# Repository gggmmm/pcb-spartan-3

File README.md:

# pcb-spartan-3

First attempt at PCB design using KiCad 5.1. This design contains Xilinx Spartan-3 programmable either through JTAG or Atmega328p.

Eeschema produces some warnings, due to the fact I have used different grids, which I learned later to be discouraged.

In the library, there are more footprints/models than actually used. I did not remove the unused ones.

Tested only on Windows 10.

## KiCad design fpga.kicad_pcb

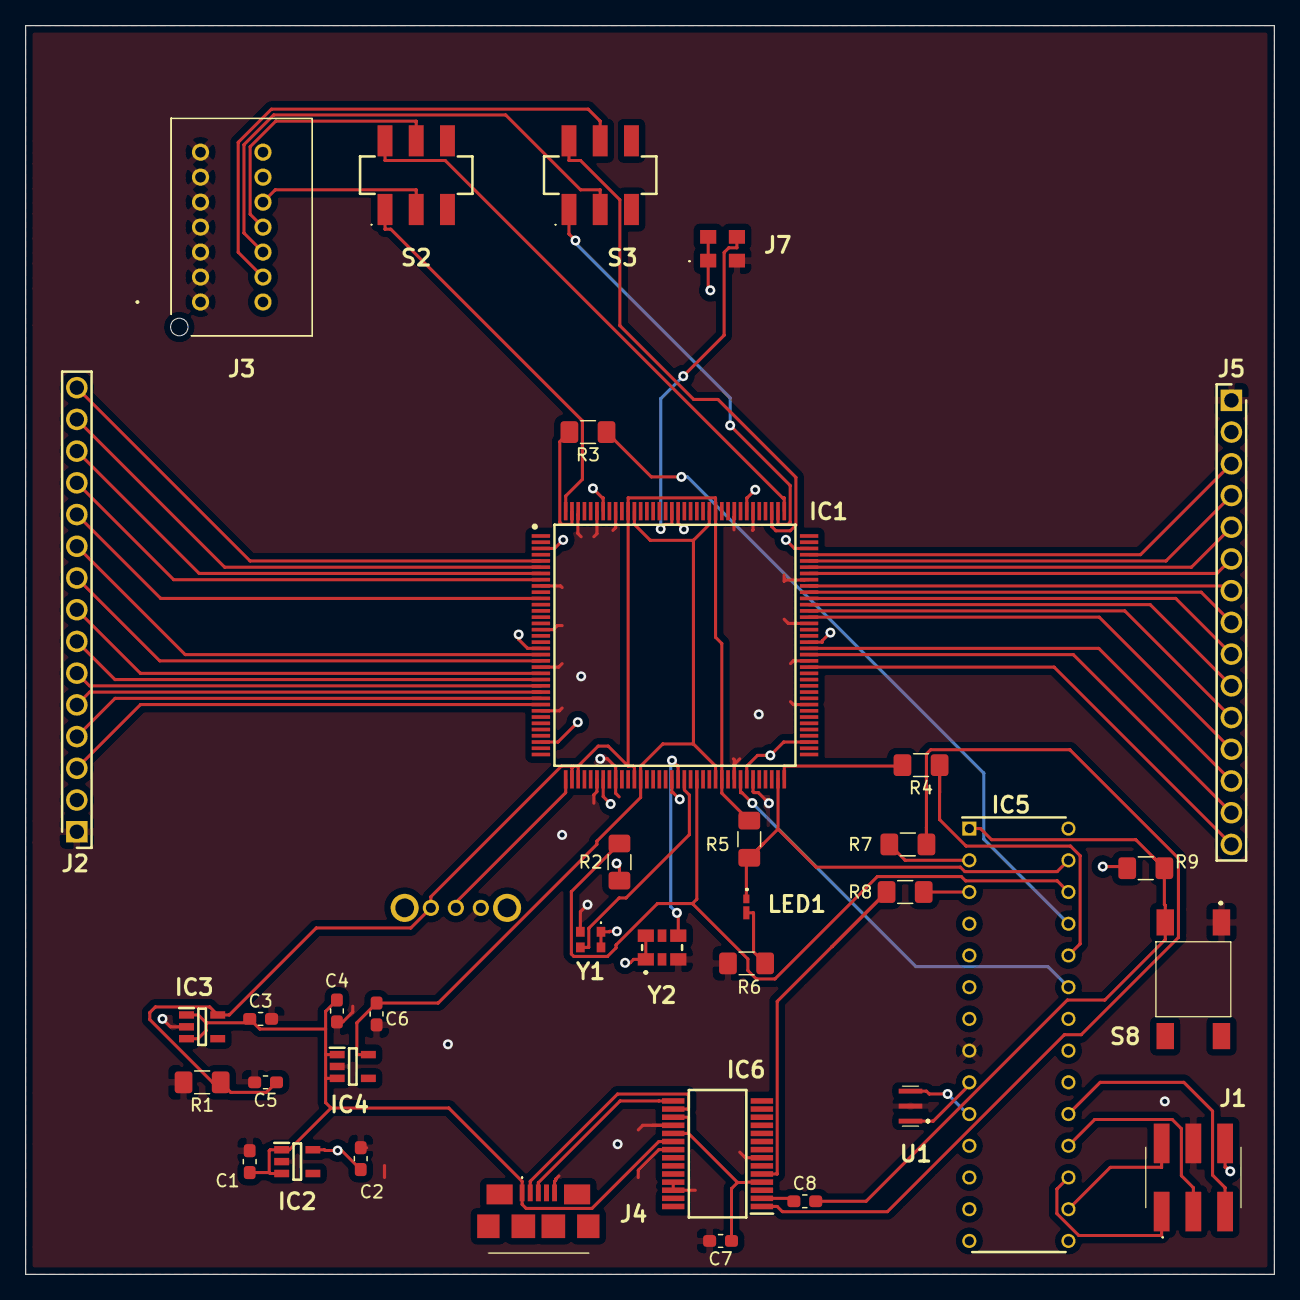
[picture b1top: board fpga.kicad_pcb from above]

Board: 4 copper layers, 100.0 x 100.0 mm, 37 parts (1 on the bottom side), 66 nets.

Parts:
C1, C2, C3, C4, C5, C6: 1uF; C_0603_1608Metric_Pad1.05x0.95mm_HandSolder
C7, C8: 100nF; C_0603_1608Metric_Pad1.05x0.95mm_HandSolder
IC1: XC3S200-4TQG144C; QFP50P2200X2200X160-144N
IC2: MIC5504-3.3YM5-TR; SOT95P280X145-5N
IC3: MIC5504-2.5YM5-T5; SOT95P280X145-5N
IC4: MIC5504-1.2YM5-TR; SOT95P280X130-5N
IC5: ATMEGA328P-PU; DIP794W53P254L3467H457Q28N
IC6: FT232RL-TUBE; SOP65P780X200-28N
J1: ICSP; 10129383906002ALF
J2: BANK 6/7; HDRV15W67P0X254_1X15_3785X236X1117P
J3: 55917-1410; 559171410
J4: ZX62-B-5PA_33_; ZX62B5PA33
J5: BANK 2/3; HDRV15W67P0X254_1X15_3785X236X1117P
J7: OSC 32.768 kHz; ECS327MVATX3CNTR
LED1: KG_DELLS1.22-JGKH-24; KGDELLS122JGKH24
R1, R3, R4: 68; R_1206_3216Metric_Pad1.42x1.75mm_HandSolder
R2: 4.7K; R_1206_3216Metric_Pad1.42x1.75mm_HandSolder
R5, R6: 330; R_1206_3216Metric_Pad1.42x1.75mm_HandSolder
R7, R8: 1K; R_1206_3216Metric_Pad1.42x1.75mm_HandSolder
R9: 10K; R_1206_3216Metric_Pad1.42x1.75mm_HandSolder
S1: M1_SW; OS102011MA1QN1
S2: SW_TDI_TDO; JS202011SCQN
S3: SW_TCK_TMS; JS202011SCQN
S8: LL3301NF065QG
U1: RESON_8M; CSTNE16M0V530000R0
Y1: OSC 50 MHz; DSC6101JL3B0500000
Y2: OSC 200 MHz; XLH335200000000X

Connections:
+1V2: C6.1, IC1.49, IC1.61, IC1.121, IC1.133, IC4.5
+2V5: C5.1, IC1.38, IC1.39, IC1.48, IC1.62, IC1.120, IC1.134, IC3.5, R1.1, R5.2, S1.1
+3V3: C2.1, IC1.3, IC1.19, IC1.34, IC1.43, IC1.54, IC1.66, IC1.75, IC1.91, IC1.106, IC1.115, IC1.126, IC1.138, IC2.5, IC5.7, IC5.20, J1.B3, J2.2, J3.2, J5.2, J7.1, J7.4, R2.1, R9.2, Y1.1, Y1.4, Y2.1, Y2.6
CCLK: IC5.24, R4.1
D+: IC6.15, J4.3
D-: IC6.16, J4.2
DIN_DO: IC1.65, IC5.23
DONE: IC1.71, IC5.27, LED1.1, R5.1
DTR: C8.1, IC6.2
GND: C1.2, C2.2, C3.2, C4.2, C5.2, C6.2, C7.2, IC1.9, IC1.16, IC1.22, IC1.29, IC1.42, IC1.45, IC1.64, IC1.67, IC1.81, IC1.88, IC1.94, IC1.101, IC1.114, IC1.117, IC1.136, IC1.139, IC1.142, IC2.2, IC3.2, IC4.2, IC5.8, IC5.22, IC6.7, IC6.18, IC6.21, IC6.25, IC6.26, J1.B2, J2.1, J3.1, J3.3, J3.5, J3.7, J3.9, J3.11, J3.13, J4.5, J5.1, J7.2, R1.2, R6.1, S1.3, S8.1, U1.2, Y1.2, Y2.3
INIT_B: IC1.58, IC5.26, R2.2
IO_L20N_2: IC1.105, J5.3
IO_L20N_7: IC1.6, J2.14
IO_L20P_2: IC1.104, J5.4
IO_L20P_7: IC1.5, J2.15
IO_L21N_2: IC1.103, J5.5
IO_L21N_7: IC1.8, J2.12
IO_L21P_2: IC1.102, J5.6
IO_L21P_7: IC1.7, J2.13
IO_L22N_2: IC1.100, J5.7
IO_L22N_6: IC1.28, J2.3
IO_L22N_7: IC1.11, J2.11
IO_L22P_2: IC1.99, J5.8
IO_L22P_6: IC1.27, J2.4
IO_L23N_2: IC1.98, J5.9
IO_L23N_6: IC1.26, J2.5
IO_L23P_2: IC1.97, J5.10
IO_L23P_6: IC1.25, J2.6
IO_L24N_2: IC1.96, J5.11
IO_L24N_3: IC1.87, J5.15
IO_L24N_6: IC1.24, J2.7
IO_L24P_2: IC1.95, J5.12
IO_L24P_6: IC1.23, J2.8
IO_L40N_3: IC1.90, J5.13
IO_L40N_6: IC1.21, J2.9
IO_L40P_3: IC1.89, J5.14
IO_L40P_6: IC1.20, J2.10
M1: IC1.37, S1.2
MCU_RESET: C8.2, IC5.1, R9.1, S8.3
MISO: IC5.18, J1.A2
MOSI: IC5.17, J1.A1
unnamed: C7.1, IC6.4, IC6.17, IC6.19
unnamed: IC1.72, R4.2
unnamed: IC1.143, R3.2
unnamed: IC5.2, R7.2
unnamed: IC5.3, R8.2
unnamed: IC5.9, U1.1
unnamed: IC5.10, U1.3
unnamed: LED1.2, R6.2
OSC_32K768: IC1.127, J7.3
OSC_50M: IC1.55, Y2.4
OSC_200M: IC1.56, Y1.3
PROG_B: IC5.25, R3.1
RXD_FROM_FT232: IC6.5, R8.1
SCK: IC5.19, J1.A3
SSB: IC5.16, J1.B1
TCK: J3.6, S3.2
TCK_TO_FPGA: IC1.110, S3.1
TDI: J3.10, S2.2
TDI_TO_FPGA: IC1.144, S2.1
TDO: J3.8, S2.5
TDO_FROM_FPGA: IC1.109, S2.6
TMS: J3.4, S3.5
TMS_TO_FPGA: IC1.111, S3.6
TXD_FROM_FT232: IC6.1, R7.1
VBUS: C1.1, C3.1, C4.1, IC2.1, IC2.3, IC3.1, IC3.3, IC4.1, IC4.3, IC6.20, J4.1

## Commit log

2021-06-06 Initial commit: schematic and layout done
2021-06-06 rotated USB connector
2022-03-29 added images
